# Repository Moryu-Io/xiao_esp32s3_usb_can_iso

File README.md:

* PlatformIO project
* Device : XIAO ESP32S4 
* CAN ISORATOR
* RS485
* DEBUG UART

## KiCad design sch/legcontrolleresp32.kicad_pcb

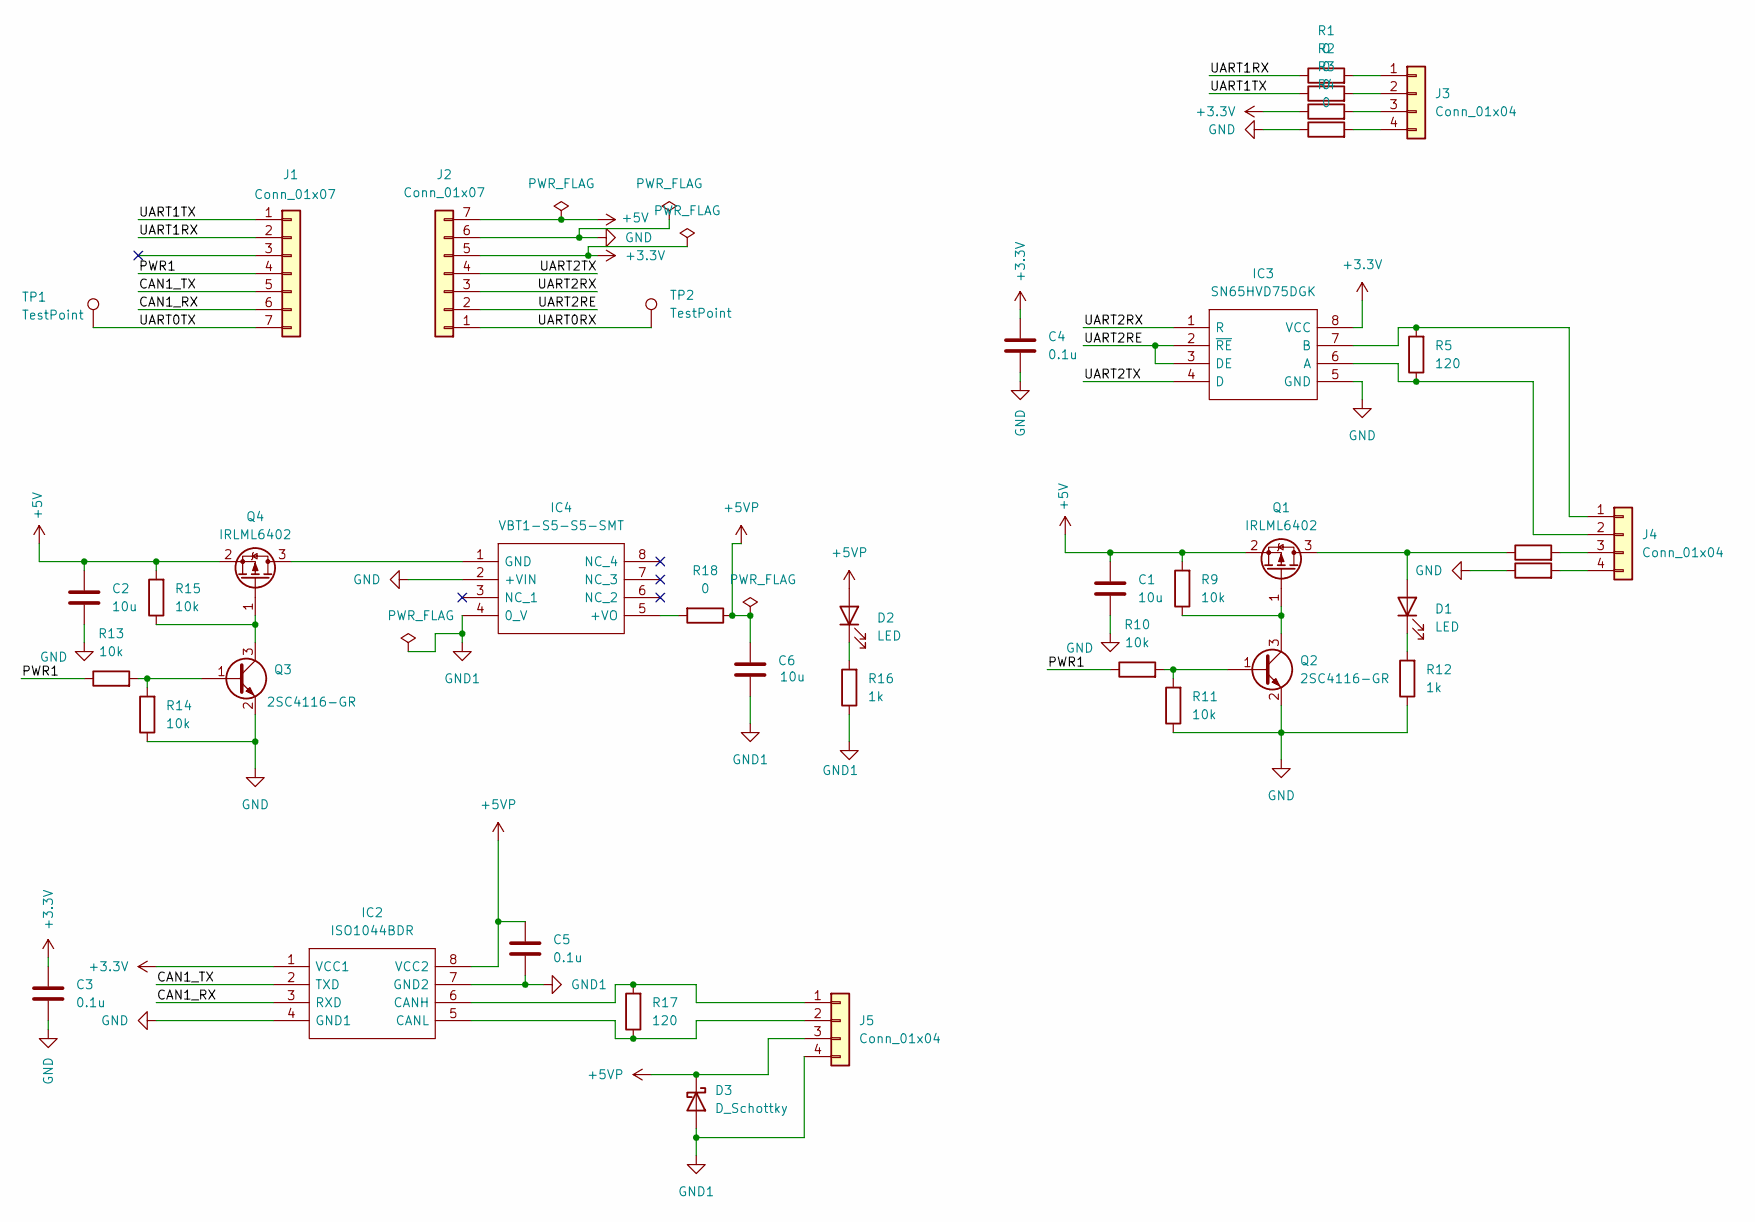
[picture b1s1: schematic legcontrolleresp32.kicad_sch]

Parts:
C1, C2, C6: 10u; C_0603_1608Metric
C3, C4, C5: 0.1u; C_0402_1005Metric
D1, D2: LED; LED_0603_1608Metric
D3: D_Schottky; D_SOD-123
IC2: ISO1044BDR; SOIC127P600X175-8N; Manufacturer_Part_Number ISO1044BDR; Mouser Part Number 595-ISO1044BDR
IC3: SN65HVD75DGK; VSSOP-8_3x3mm_P0.65mm; Mouser Part Number 595-SN65HVD485EDGKR
IC4: VBT1-S5-S5-SMT; SOP254P1120X625-8N; Mouser Part Number 490-VBT1-S5-S5-SMT
J1, J2: Conn_01x07; PinHeader_1x07_P2.54mm_Vertical
J3, J4: Conn_01x04; JST_ZH_B4B-ZR_1x04_P1.50mm_Vertical
J5: Conn_01x04; JST_PH_B4B-PH-K_1x04_P2.00mm_Vertical
Q1, Q4: IRLML6402; SOT-23
Q2, Q3: 2SC4116-GR; SOT-323_SC-70
R1, R2, R3, R4, R7, R8, R18: 0; R_0402_1005Metric
R5, R17: 120; R_0402_1005Metric
R9, R10, R11, R13, R14, R15: 10k; R_0402_1005Metric
R12, R16: 1k; R_0402_1005Metric
TP1, TP2: TestPoint; TestPoint_Pad_D1.5mm

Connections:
+3.3V: C3.1, C4.1, IC2.1 (VCC1), IC3.8 (VCC), J2.5, R3.1
+5V: C1.1, C2.1, J2.7, Q1.2 (S), Q4.2 (S), R9.2, R15.2
+5VP: C5.1, C6.1, D2.2 (A), D3.1 (K), IC2.8 (VCC2), J5.3, R18.1
/CAN1_RX: IC2.3 (RXD), J1.6
/CAN1_TX: IC2.2 (TXD), J1.5
/PWR1: J1.4, R10.1, R13.1
/UART0RX: J2.1, TP2.1
/UART0TX: J1.7, TP1.1
/UART1RX: J1.2, R1.1
/UART1TX: J1.1, R2.1
/UART2RE: IC3.2 (~RE), IC3.3 (DE), J2.2
/UART2RX: IC3.1 (R), J2.3
/UART2TX: IC3.4 (D), J2.4
GND: C1.2, C2.2, C3.2, C4.2, IC2.4 (GND1), IC3.5 (GND), IC4.2 (+VIN), J2.6, Q2.2 (E), Q3.2 (E), R4.1, R8.1, R11.1, R12.1, R14.1
GND1: C5.2, C6.2, D3.2 (A), IC2.7 (GND2), IC4.4 (0_V), J5.4, R16.1
unnamed: D1.2 (A), Q1.3 (D), R7.1
unnamed: D1.1 (K), R12.2
unnamed: D2.1 (K), R16.2
unnamed: IC2.6 (CANH), J5.1, R17.2
unnamed: IC2.5 (CANL), J5.2, R17.1
unnamed: IC3.6 (A), J4.2, R5.1
unnamed: IC3.7 (B), J4.1, R5.2
unnamed: IC4.5 (+VO), R18.2
unnamed: IC4.1 (GND), Q4.3 (D)
unnamed: J3.1, R1.2
unnamed: J3.2, R2.2
unnamed: J3.3, R3.2
unnamed: J3.4, R4.2
unnamed: J4.3, R7.2
unnamed: J4.4, R8.2
unnamed: Q1.1 (G), Q2.3 (C), R9.1
unnamed: Q2.1 (B), R10.2, R11.2
unnamed: Q3.1 (B), R13.2, R14.2
unnamed: Q3.3 (C), Q4.1 (G), R15.1

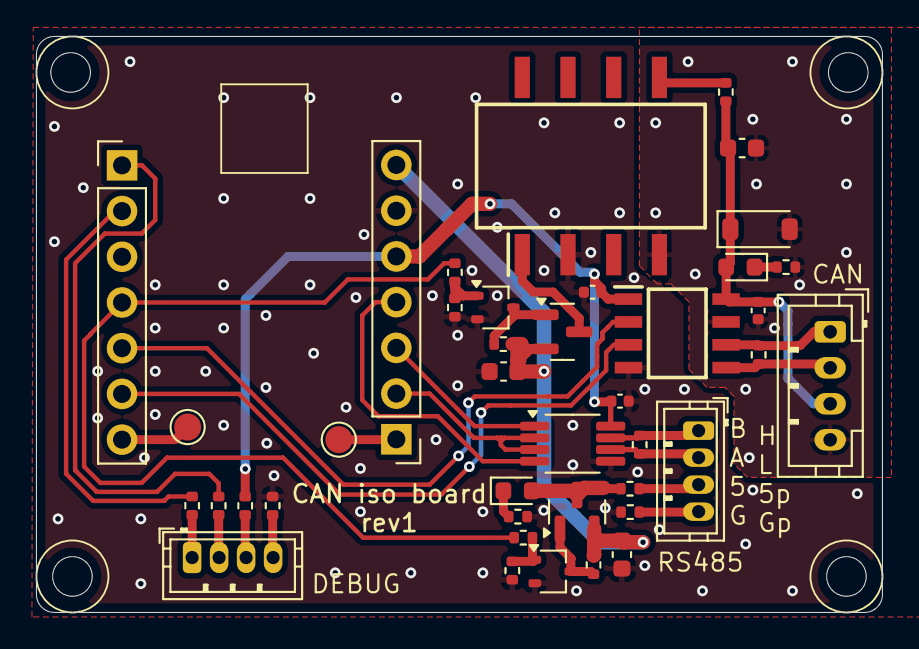
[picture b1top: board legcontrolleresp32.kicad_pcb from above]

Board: 2 copper layers, 47.0 x 32.0 mm, 40 parts (0 on the bottom side), 34 nets.

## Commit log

2024-09-29 add readme
2024-09-29 fix : stack consumption
2024-10-24 can transmit test
2025-02-09 microrosarduino
2025-02-10 robot manage task
2025-02-10 add init function
    release init function from loop task in RTOS
2025-02-10 add some code
2025-02-10 feat : microros reconnection
2025-03-29 hoge
